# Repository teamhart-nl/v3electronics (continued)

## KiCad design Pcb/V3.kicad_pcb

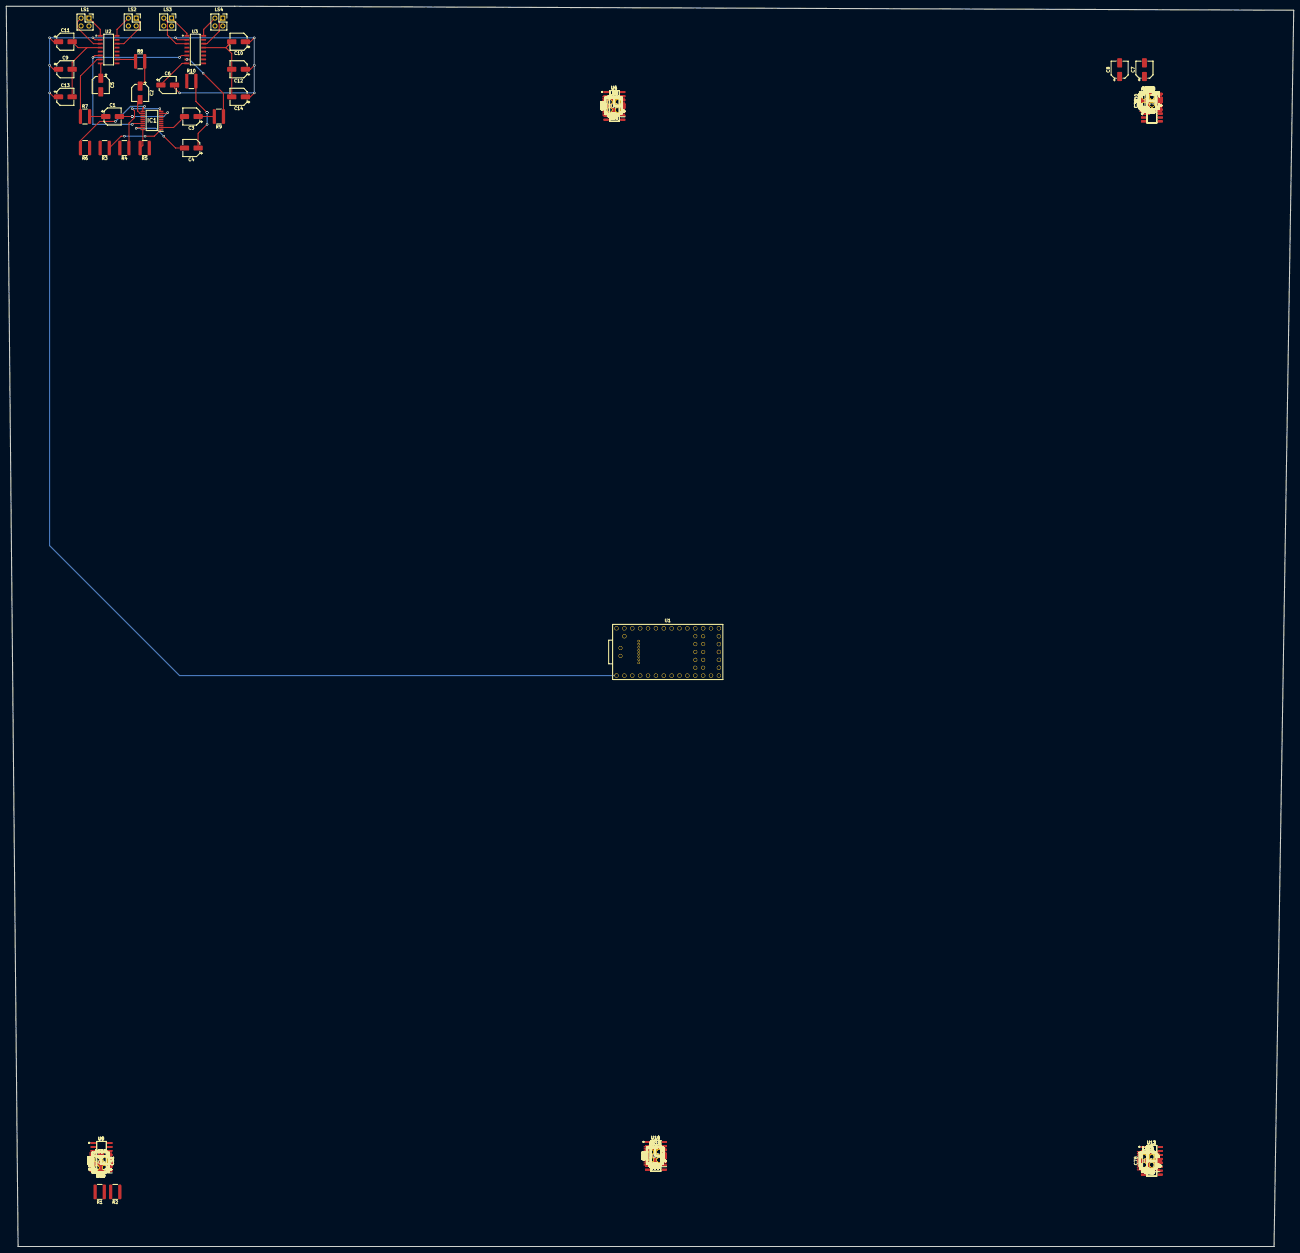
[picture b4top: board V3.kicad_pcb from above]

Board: 2 copper layers, 415.3 x 400.1 mm, 187 parts (0 on the bottom side), 190 nets.

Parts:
C1, C2, C3, C4, C15, C16, C17, C18, C29, C30, C31, C32, C43, C44, C45, C46, C57, C58, C59, C60, C71, C72, C73, C74: 0.47uF; CP_Elec_5x5.9
C5, C6, C19, C20, C33, C34, C47, C48, C61, C62, C75, C76: 0.1uF; CP_Elec_5x5.9
C7, C8, C9, C10, C13, C14, C21, C22, C23, C24, C27, C28, C35, C36, C37, C38, C41, C42, C49, C50, C51, C52, C55, C56, C63, C64, C65, C66, C69, C70, C77, C78, C79, C80, C83, C84: 1uF; CP_Elec_5x5.9
C11, C12, C25, C26, C39, C40, C53, C54, C67, C68, C81, C82: 470uF; CP_Elec_5x5.9
IC1, IC2, IC3, IC4, IC5, IC6: MCP4451-103E_ST; SOP65P640X120-20N
LS1, LS2, LS3, LS4, LS5, LS6, LS7, LS8, LS9, LS10, LS11, LS12, LS13, LS14, LS15, LS16, LS17, LS18, LS19, LS20, LS21, LS22, LS23, LS24: Speaker; PinSocket_2x02_P2.54mm_Vertical
R1, R2, R11, R12, R21, R22, R31, R32, R41, R42, R51, R52: 2200; R_1218_3246Metric
R3, R4, R5, R6, R13, R14, R15, R16, R23, R24, R25, R26, R33, R34, R35, R36, R43, R44, R45, R46, R53, R54, R55, R56: 51000; R_1218_3246Metric
R7, R8, R9, R10, R17, R18, R19, R20, R27, R28, R29, R30, R37, R38, R39, R40, R47, R48, R49, R50, R57, R58, R59, R60: 10000; R_1218_3246Metric
U1: Teensy4.0; Teensy40_SMT
U2, U3, U4, U5, U6, U7, U8, U9, U10, U11, U12, U13: PAM8403; SOIC127P605X150-16N

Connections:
FREQ1: R6.1, U1.4
FREQ2: R4.2, U1.6
FREQ3: R5.1, U1.7
FREQ4: R3.2, U1.8
FREQ5: R16.1, U1.9
FREQ6: R14.2, U1.12
FREQ7: R15.1, U1.13
FREQ8: R13.2, U1.14
FREQ9: R24.2, R26.1, U1.20
FREQ10: R23.2, R25.1, U1.21
FREQ11: R34.2, R36.1, U1.22
FREQ12: R33.2, R35.1, U1.29
FREQ13: R44.2, R46.1, U1.39
FREQ14: R43.2, R45.1, U1.45
FREQ15: R54.2, R56.1, U1.48
FREQ16: R53.2, R55.1, U1.50
unnamed: C1.1, R7.2
unnamed: C1.2, IC1.9
unnamed: C2.1, R8.2
unnamed: C2.2, IC1.12
unnamed: C3.1, R9.2
unnamed: C3.2, IC1.2
unnamed: C4.1, R10.2
unnamed: C4.2, IC1.19
unnamed: C5.1, U2.8
unnamed: C6.1, U3.8
unnamed: C10.2, C12.2, C14.2, U3.4, U3.13
unnamed: C9.2, C11.2, C13.2, U2.4, U2.13
unnamed: C15.1, R17.2
unnamed: C15.2, IC2.9
unnamed: C16.1, R18.2
unnamed: C16.2, IC2.12
unnamed: C17.1, R19.2
unnamed: C17.2, IC2.2
unnamed: C18.1, R20.2
unnamed: C18.2, IC2.19
unnamed: C19.1, U4.8
unnamed: C20.1, U5.8
unnamed: C23.2, C25.2, C27.2, U4.4, U4.13
unnamed: C24.2, C26.2, C28.2, U5.4, U5.13
unnamed: C29.1, R27.2
unnamed: C29.2, IC3.9
unnamed: C30.1, R28.2
unnamed: C30.2, IC3.12
unnamed: C31.1, R29.2
unnamed: C31.2, IC3.2
unnamed: C32.1, R30.2
unnamed: C32.2, IC3.19
unnamed: C33.1, U6.8
unnamed: C34.1, U7.8
unnamed: C37.2, C39.2, C41.2, U6.4, U6.13
unnamed: C38.2, C40.2, C42.2, U7.4, U7.13
unnamed: C43.1, R37.2
unnamed: C43.2, IC4.9
unnamed: C44.1, R38.2
unnamed: C44.2, IC4.12
unnamed: C45.1, R39.2
unnamed: C45.2, IC4.2
unnamed: C46.1, R40.2
unnamed: C46.2, IC4.19
unnamed: C47.1, U8.8
unnamed: C48.1, U9.8
unnamed: C51.2, C53.2, C55.2, U8.4, U8.13
unnamed: C52.2, C54.2, C56.2, U9.4, U9.13
unnamed: C57.1, R47.2
unnamed: C57.2, IC5.9
unnamed: C58.1, R48.2
unnamed: C58.2, IC5.12
unnamed: C59.1, R49.2
unnamed: C59.2, IC5.2
unnamed: C60.1, R50.2
unnamed: C60.2, IC5.19
unnamed: C61.1, U10.8
unnamed: C62.1, U11.8
unnamed: C65.2, C67.2, C69.2, U10.4, U10.13
unnamed: C66.2, C68.2, C70.2, U11.4, U11.13
unnamed: C71.1, R57.2
unnamed: C71.2, IC6.9
unnamed: C72.1, R58.2
unnamed: C72.2, IC6.12
unnamed: C73.1, R59.2
unnamed: C73.2, IC6.2
unnamed: C74.1, R60.2
unnamed: C74.2, IC6.19
unnamed: C75.1, U12.8
unnamed: C76.1, U13.8
unnamed: C79.2, C81.2, C83.2, U12.4, U12.13
unnamed: C80.2, C82.2, C84.2, U13.4, U13.13
unnamed: IC1.1, R3.1
unnamed: IC1.10, R4.1
unnamed: IC1.11, R6.2
unnamed: IC1.20, R5.2
unnamed: IC2.1, R13.1
unnamed: IC2.10, R14.1
unnamed: IC2.11, R16.2
unnamed: IC2.20, R15.2
unnamed: IC3.1, R23.1
unnamed: IC3.10, R24.1
unnamed: IC3.11, R26.2
unnamed: IC3.20, R25.2
unnamed: IC4.1, R33.1
unnamed: IC4.10, R34.1
unnamed: IC4.11, R36.2
unnamed: IC4.20, R35.2
unnamed: IC5.1, R43.1
unnamed: IC5.10, R44.1
unnamed: IC5.11, R46.2
unnamed: IC5.20, R45.2
unnamed: IC6.1, R53.1
unnamed: IC6.10, R54.1
unnamed: IC6.11, R56.2
unnamed: IC6.20, R55.2
unnamed: LS1.1, U2.1
unnamed: LS1.2, U2.3
unnamed: LS2.1, U2.14
unnamed: LS2.2, U2.16
unnamed: LS3.1, U3.1
unnamed: LS3.2, U3.3
unnamed: LS4.1, U3.14
unnamed: LS4.2, U3.16
unnamed: LS5.1, U4.1
unnamed: LS5.2, U4.3
unnamed: LS6.1, U4.14
unnamed: LS6.2, U4.16
unnamed: LS7.1, U5.1
unnamed: LS7.2, U5.3
unnamed: LS8.1, U5.14
unnamed: LS8.2, U5.16
unnamed: LS9.1, U6.1
unnamed: LS9.2, U6.3
unnamed: LS10.1, U6.14
unnamed: LS10.2, U6.16
unnamed: LS11.1, U7.1
unnamed: LS11.2, U7.3
unnamed: LS12.1, U7.14
unnamed: LS12.2, U7.16
unnamed: LS13.1, U8.1
unnamed: LS13.2, U8.3
unnamed: LS14.1, U8.14
unnamed: LS14.2, U8.16
unnamed: LS15.1, U9.1
unnamed: LS15.2, U9.3
unnamed: LS16.1, U9.14
unnamed: LS16.2, U9.16
unnamed: LS17.1, U10.1
unnamed: LS17.2, U10.3
unnamed: LS18.1, U10.14
unnamed: LS18.2, U10.16
unnamed: LS19.1, U11.1
unnamed: LS19.2, U11.3
unnamed: LS20.1, U11.14
unnamed: LS20.2, U11.16
unnamed: LS21.1, U12.1
unnamed: LS21.2, U12.3
unnamed: LS22.1, U12.14
unnamed: LS22.2, U12.16
unnamed: LS23.1, U13.1
unnamed: LS23.2, U13.3
unnamed: LS24.1, U13.14
unnamed: LS24.2, U13.16
unnamed: R7.1, U2.7
unnamed: R8.1, U2.10
unnamed: R9.1, U3.7
unnamed: R10.1, U3.10
unnamed: R17.1, U4.7
unnamed: R18.1, U4.10
unnamed: R19.1, U5.7
unnamed: R20.1, U5.10
unnamed: R27.1, U6.7
unnamed: R28.1, U6.10
unnamed: R29.1, U7.7
unnamed: R30.1, U7.10
unnamed: R37.1, U8.7
unnamed: R38.1, U8.10
unnamed: R39.1, U9.7
unnamed: R40.1, U9.10
unnamed: R47.1, U10.7
unnamed: R48.1, U10.10
unnamed: R49.1, U11.7
unnamed: R50.1, U11.10
unnamed: R57.1, U12.7
unnamed: R58.1, U12.10
unnamed: R59.1, U13.7
unnamed: R60.1, U13.10
SCL0: IC1.5, IC2.5, IC3.5, IC4.5, R1.1, R11.1, R21.1, R31.1, U1.26
SCL1: IC5.5, IC6.5, R41.1, R51.1, U1.23
SDA0: IC1.6, IC2.6, IC3.6, IC4.6, R2.1, R12.1, R22.1, R32.1, U1.25
SDA1: IC5.6, IC6.6, R42.1, R52.1, U1.24
TeensyGND: C5.2, C6.2, C7.1, C8.1, C9.1, C10.1, C11.1, C12.1, C13.1, C14.1, C19.2, C20.2, C21.1, C22.1, C23.1, C24.1, C25.1, C26.1, C27.1, C28.1, C33.2, C34.2, C35.1, C36.1, C37.1, C38.1, C39.1, C40.1, C41.1, C42.1, C47.2, C48.2, C49.1, C50.1, C51.1, C52.1, C53.1, C54.1, C55.1, C56.1, C61.2, C62.2, C63.1, C64.1, C65.1, C66.1, C67.1, C68.1, C69.1, C70.1, C75.2, C76.2, C77.1, C78.1, C79.1, C80.1, C81.1, C82.1, C83.1, C84.1, IC1.3, IC1.4, IC1.7, IC1.8, IC1.13, IC1.16, IC1.18, IC2.3, IC2.4, IC2.7, IC2.8, IC2.13, IC2.16, IC2.18, IC3.3, IC3.4, IC3.7, IC3.8, IC3.13, IC3.16, IC3.18, IC4.3, IC4.4, IC4.7, IC4.8, IC4.13, IC4.16, IC4.18, IC5.3, IC5.4, IC5.7, IC5.8, IC5.13, IC5.16, IC5.18, IC6.3, IC6.4, IC6.7, IC6.8, IC6.13, IC6.16, IC6.18, U1.1, U2.2, U2.11, U2.15, U3.2, U3.11, U3.15, U4.2, U4.11, U4.15, U5.2, U5.11, U5.15, U6.2, U6.11, U6.15, U7.2, U7.11, U7.15, U8.2, U8.11, U8.15, U9.2, U9.11, U9.15, U10.2, U10.11, U10.15, U11.2, U11.11, U11.15, U12.2, U12.11, U12.15, U13.2, U13.11, U13.15
TeensyVDD: C7.2, C8.2, C21.2, C22.2, C35.2, C36.2, C49.2, C50.2, C63.2, C64.2, C77.2, C78.2, IC1.17, IC2.17, IC3.17, IC4.17, IC5.17, IC6.17, R1.2, R2.2, R11.2, R12.2, R21.2, R22.2, R31.2, R32.2, R41.2, R42.2, R51.2, R52.2, U1.31, U2.6, U3.6, U4.6, U5.6, U6.6, U7.6, U8.6, U9.6, U10.6, U11.6, U12.6, U13.6

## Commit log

2021-05-10 Added teensy library
2021-05-10 Added other libraries
2021-05-10 Add V3 basic layout
2021-05-11 First version of first module
2021-05-11 Some small changes
2021-05-11 Small optimizations
2021-05-15 Added all different pots and amps and connected them to the correct frequency pins
2021-05-24 Update SCH to include hierachical pages and remove most ERC errors
2021-05-24 Export netlist
2021-05-28 Update symbols and begin PCB
2021-05-31 Updated folder structure to work better with KiCad and rough layout done
2021-06-10 Some progress before reverting to 3/3 i2c line
2021-06-10 Finalize PCB v0
2021-06-17 Finalize PCB
2021-06-17 Add updated PCB
2021-06-19 Add HARTware pun
2021-06-25 Release V3.0.1
2021-06-25 Fixed bottom refdes text
2021-08-29 Clean V3.0
2021-08-29 V3 top done
2021-08-29 Add bottom PCB WIP
2021-08-30 Updated BOT
2021-08-31 Done BOT v3.1
2021-11-26 Cleanup symbols and libraries and add separate submodule for kicad-libaries
2021-11-28 V3.2 start
2021-12-09 Add bom
2022-03-24 Create LICENSE
